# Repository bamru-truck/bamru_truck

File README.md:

# Bamru Truck Wifi Hotspot and Microserver

This guide assumes you've got an Ubuntu laptop with an SD card reader/writer,
and a RPi2 with a USB-WIFI device that runs in master mode.

Github Repo: `https://github.com/cinchcircuits/bamru_truck.git`

The key tools we use to build and maintain the Hotspot:
```
+-------------------+-------------------------------+
| Function          | Tool                          |
+-------------------+-------------------------------+
| RPi configuration | Ansible                       |
| Scripting         | Bash                          |
| Web-Admin UI      | Ruby / Sinatra                |
| Remote pairing    | Tmux / Vim / Wemux            |
+-------------------+-------------------------------+
```

## New RPi Setup

1) load Raspian onto a SD card

https://www.raspberrypi.org/documentation/installation/installing-images/README.md

2) boot the new RPi

3) set the passwd of the 'pi' user to 'pi'

4) enable SSH on the RPi

5) choose a unique hostname & setup DNS or /etc/hosts with the RPi name/address

6) plug in the USB-WIFI and an ethernet cable

7) now you should be able to `ssh pi@<hostname>`

ProTip: create a reusable OS image pre-configured with passwords and account
settings.  Ask Andy for more info.

## Ansible Configuration

1) install latest version of Ansible to your Ubuntu laptop

http://docs.ansible.com/intro_installation.html#latest-releases-via-apt-ubuntu

2) clone the repo and CD to the `playbooks` directory

3) edit `inventory/hosts-<your_username>.ini` - add the RPi hostname and SSID

4) run `./config` to load a bunch of software and configure the hotspot

Notes:
- user-account passwords will be set to 'BamruTruck'

## Using the RPi hotspot

1) You should see the RPi SSID on your laptop network chooser

2) RPi Wifi Passwd is `werescue`

3) You should connect and get a IP address (view with `ifconfig`)

4) Your wifi connection speed should be as good as a commercial hotspot

## Adding a GPS to your hotspot

1) https://github.com/cinchcircuits/bamru_truck/blob/master/playbooks/roles/gpsd

## Adding and using a 2g/3g/4g cell modem to your device

1) https://github.com/cinchcircuits/bamru_truck/tree/master/playbooks/roles/cell_modem_support

## How to Contribute

You'll need a GitHub account, Ubuntu, Command Line savvy, networking skills,
Raspberry Pi know-how, and basic coding skills (HTML, CSS, JS, Ruby).

[Contributing](./docs/Contributing.md)

[Development Notes](./docs/Notes.md)

[Pair Programming](./docs/PairProgramming.md)

[Jenkins](./docs/Jenkins.md)

[Configuring Hostapd and DnsMasq](./docs/HostapdDnsmasq.md)

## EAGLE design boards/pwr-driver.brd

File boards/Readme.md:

-- Rpi Power board

Version 0.1 features:

 - onboard battery support for remote operation
 - ADC (voltage monitor) for incoming voltage and onboard battery. 
 - Ignition detection support
 - Mosfet cutoffs for disconnecting battery and power when battery voltages get low
 - onboard temp monitor
 - onboard RTC support
 - pass through usb connector for powering off cell router
 - Onboard rgb led for use as status indicator. 
 - Unfortunate high current draw at power off (~10 ma). Not green at all, and a concern if the truck is going to go unpowered for many weeks or months. Can run a full car battery dead in 9 months, or make for a slower start after 2 months. 

Possible version 1.0 features:
 - Onboard moisture/humidity sensor
 - onboard gps sensor (not USB)
 - Lower current draw at power off. Shooting for no more than 1 ma.

-- Version 0.1 produced board details
The board has the following features
 - 12v to 4.2 volt step down to charge battery (MPM80)
 - li+ to 5 volt dc to dc (ebay special)
 - can power RPi off of LI+ cell
 - onboard temp monitor LM75b
 - onboard RTC DS1340(DS1370 compatable)
 - onboard adc ads1013

Parts list:
| Part | MPN | link
R3 | 2.2k 0603 | none
R4 | 2.2k 0603 | none
R5 | 20k 0603 | none
R6 | 10k 0603 | none
R7 | 4125 ohm 0603 | http://www.digikey.com/product-detail/en/RR0816P-4121-D-60H/RR08P4.12KDCT-ND/1288210
R8 | 1k 0603 | none
R9 | 5.5k 0603 | none
R10 | 10k 0603 | none
R11 | 30K 0603 | none
R12 | 20k 0603 | none
R13 | 5.5k 0604 | none
RTC | DS1340 | http://www.digikey.com/product-detail/en/DS1340Z-33%2BT%26R/DS1340Z-33%2BT%26RCT-ND/3647911
TEMP | LM75b | http://www.digikey.com/product-detail/en/LM75BD,118/568-4688-1-ND/1993025
ADC | 12-bit ADC | https://www.digikey.com/product-detail/en/ADS1015IDGST/296-25227-1-ND/2174997
PTC | Input protection PTC | http://www.digikey.com/scripts/DkSearch/dksus.dll?Detail&itemSeq=181553660
step-down | 5-15 to 4.2 V | http://www.digikey.com/scripts/DkSearch/dksus.dll?Detail&itemSeq=181553821
Diode | Input diode | http://www.digikey.com/scripts/DkSearch/dksus.dll?Detail&itemSeq=181553817
crystal | RTC crystal | http://www.digikey.com/product-detail/en/AB38T-32.768KHZ/535-9034-ND/675229
RTC cap | supercap for RTC | http://www.digikey.com/product-detail/en/DCK-3R3E224U-E/604-1007-ND/970168

-- I needed to build new modules for this board. 

To do this I did the following steps:
 - upgrade gcc https://somewideopenspace.wordpress.com/2014/02/28/gcc-4-8-on-raspberry-pi-wheezy/
 - did a yum update
 - yum upgrade
 - reboot
 - rpi-update
 - reboot
 - Pulled current kernel source with https://github.com/notro/rpi-source/wiki
 - Specifically: sudo wget https://raw.githubusercontent.com/notro/rpi-source/master/rpi-source -O /usr/bin/rpi-source && sudo chmod +x /usr/bin/rpi-source && /usr/bin/rpi-source -q --tag-update
 - sudo modprobe configs
 - cd to downloaded source folder
 - cp /proc/config.gz .
 - gzip -d config.gz 
 - cat ./config.gz > ./.config
 - make menuconfig
 - enable modules
 - build.. blah blah blah

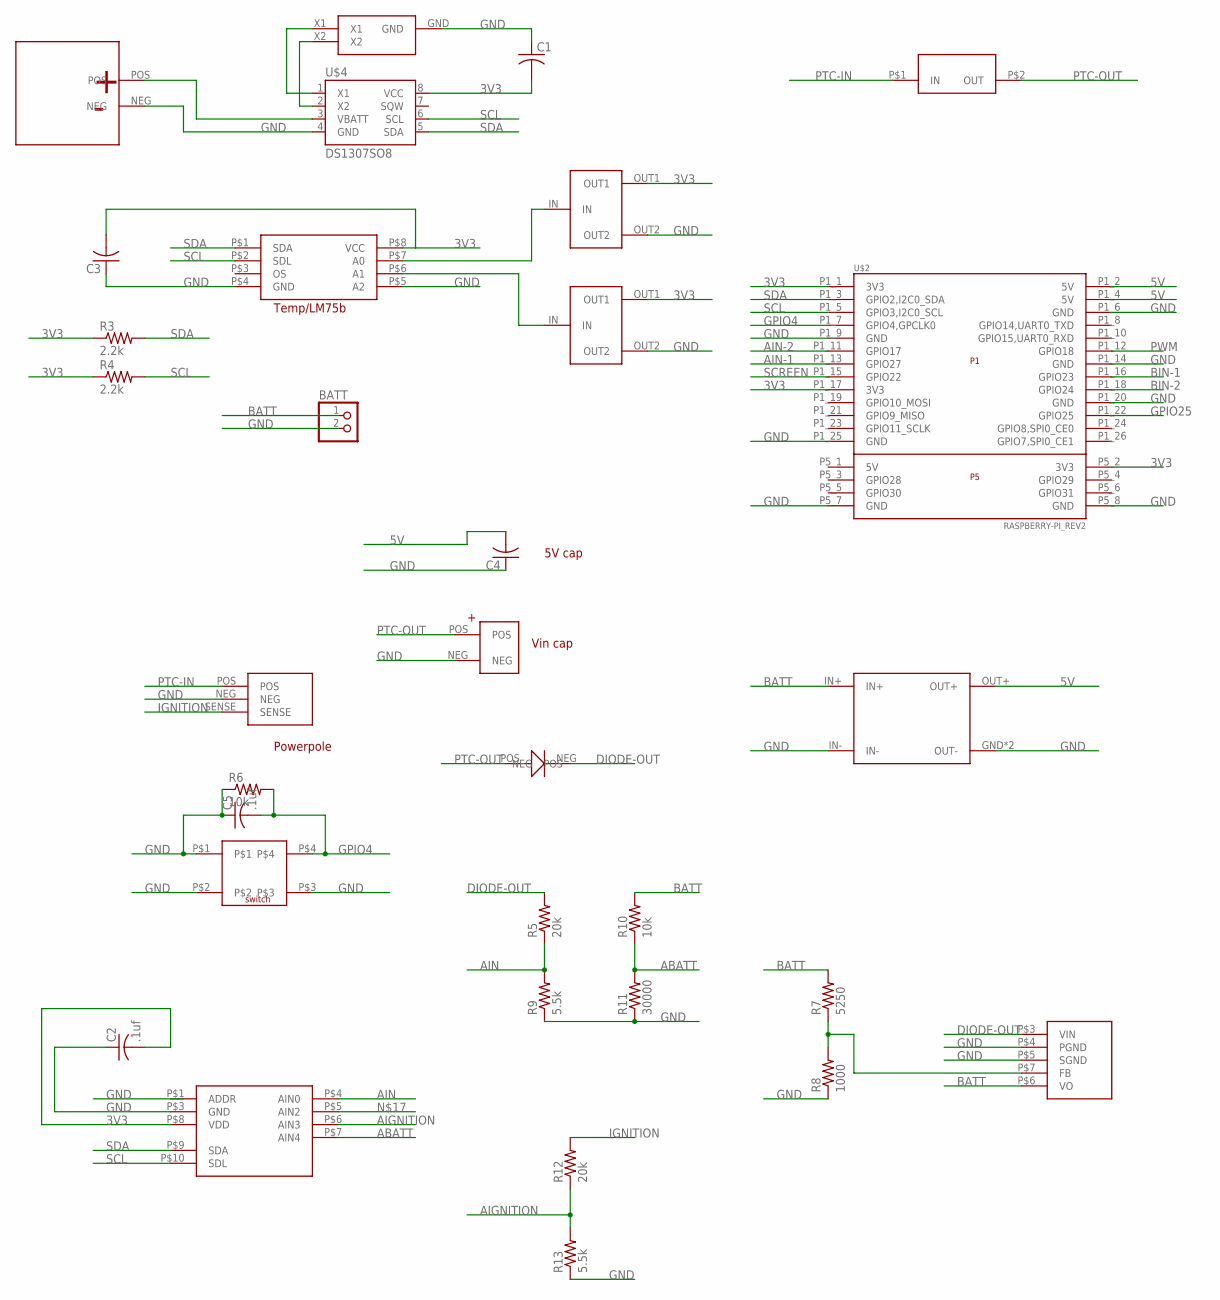
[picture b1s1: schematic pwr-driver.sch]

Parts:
BATT: PINHD-1X2; 1X02
C1: C-USC0805K; C0805K
C2, C5: .1uf; C0603
C3: C-USC0805; C0805
C4: C-USC3216; C3216
R3, R4: 2.2k; R0603
R5, R12: 20k; R0603
R6, R10: 10k; R0603
R7: 5250; R0603
R8: 1000; R0603
R9, R13: 5.5k; R0603
R11: 30000; R0603
U$1: MPM80; TO-220-8L
U$2: RASPBERRY-PI_REV2
U$3: STEP-UP-FROM-AMAZON
U$4: DS1307SO8; SO08
U$5: BATTERY-MS518SE; BATTERY-MS518SE-FL35E
U$6: AB26T-CRYSTAL
U$7: POWERPOLE-WITH-SENSE; POWERPOLE-3
U$8: PTC; PTC-0ZRM0100FF1E
U$9: LM75-BDP-TEMP; TSSOP8
U$10: ADS1013; MSOP-10
U$11: CAP-SMD-100U; CAP-100UF-SMD
U$12, U$13: 0805-3-WAY
U$14: MICRO-SWITCH; BUTTON-MICRO-SWITCH
U$15: DIODE-403; 403

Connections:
3V3: C1.2, C2.2, C3.2, R3.1, R4.1, U$2.P1_1 (3V3), U$2.P1_17 (3V3), U$2.P5_2 (3V3), U$4.8 (VCC), U$9.P$8 (VCC), U$10.P$8 (VDD), U$12.OUT1, U$13.OUT1
5V: C4.2, U$2.P1_2 (5V), U$2.P1_4 (5V), U$3.OUT+
ABATT: R10.1, R11.2, U$10.P$7 (AIN4)
AIGNITION: R12.1, R13.2, U$10.P$6 (AIN3)
AIN: R5.1, R9.2, U$10.P$4 (AIN0)
AIN-1: U$2.P1_13 (GPIO27)
AIN-2: U$2.P1_11 (GPIO17)
BATT: BATT.1, R7.2, R10.2, U$1.P$6 (VO), U$3.IN+
BIN-1: U$2.P1_16 (GPIO23)
BIN-2: U$2.P1_18 (GPIO24)
DIODE-OUT: R5.2, U$1.P$3 (VIN), U$15.NEG
GND: BATT.2, C1.1, C2.1, C3.1, C4.1, C5.1, R6.1, R8.1, R9.1, R11.1, R13.1, U$1.P$4 (PGND), U$1.P$5 (SGND), U$2.P1_6 (GND), U$2.P1_9 (GND), U$2.P1_14 (GND), U$2.P1_20 (GND), U$2.P1_25 (GND), U$2.P5_7 (GND), U$2.P5_8 (GND), U$3.GND (OUT-), U$3.IN-, U$3.OUT-, U$4.4 (GND), U$5.NEG, U$6.GND, U$7.NEG, U$9.P$4 (GND), U$9.P$5 (A2), U$10.P$3 (GND), U$11.NEG, U$12.OUT2, U$13.OUT2, U$14.P$1, U$14.P$2, U$14.P$3
GPIO4: C5.2, R6.2, U$2.P1_7 (GPIO4,GPCLK0), U$14.P$4
GPIO25: U$2.P1_22 (GPIO25)
IGNITION: R12.2, U$7.SENSE
unnamed: U$4.3 (VBATT), U$5.POS
unnamed: U$4.2 (X2), U$6.X2
unnamed: U$4.1 (X1), U$6.X1
unnamed: R7.1, R8.2, U$1.P$7 (FB)
unnamed: U$9.P$7 (A0), U$12.IN
unnamed: U$9.P$6 (A1), U$13.IN
PTC-IN: U$7.POS, U$8.P$1 (IN)
PTC-OUT: U$8.P$2 (OUT), U$11.POS, U$15.POS
PWM: U$2.P1_12 (GPIO18)
SCL: R4.2, U$2.P1_5 (GPIO3,I2C0_SCL), U$4.6 (SCL), U$9.P$2 (SDL), U$10.P$10 (SDL)
SCREEN: U$2.P1_15 (GPIO22)
SDA: R3.2, U$2.P1_3 (GPIO2,I2C0_SDA), U$4.5 (SDA), U$9.P$1 (SDA), U$10.P$9 (SDA)

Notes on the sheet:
5V cap
Vin cap
Powerpole

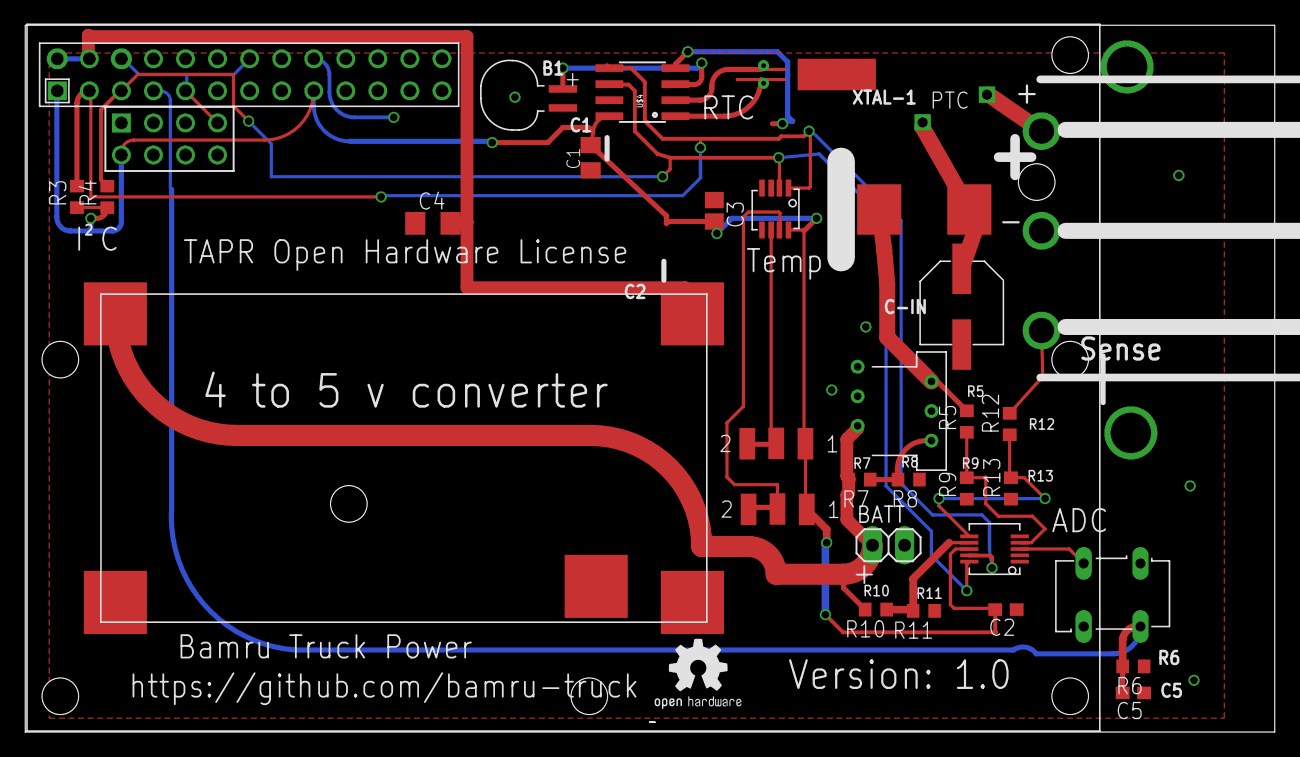
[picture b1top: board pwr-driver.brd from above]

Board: 2 copper layers, 99.0 x 56.0 mm, 33 parts (0 on the bottom side), 20 nets.

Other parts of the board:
U$16: OSHW2

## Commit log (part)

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2015-04-18 first test file
2015-05-03 initial checkin
    Added three new directories:
    1) playbooks - for ansible config stuff
    2) bin - for config scripts TBD
    3) app - for a web app TBD
2015-05-03 updated README instructions
2015-05-03 changed hostnames from rpi to bam
2015-05-03 added apt_update
2015-05-03 add a patch for the broken init.d/hostapd config
2015-05-03 tweak hotspot config
2015-05-04 fix typo
2015-05-04 added ansible_ssh_user
    This eliminates the need to edit the username in the playbook file.
2015-05-04 updated README and config script
2015-05-04 added Hacker Notes
2015-05-04 README tweaks
2015-05-04 tweak playbook
2015-05-05 updated rpi setup
2015-05-07 Ading lines to change destination for iptables rules
2015-05-08 added placeholders for diagnostic scripts
2015-05-10 Added back of hostapd to install.
2015-05-12 modprobe ip_tables
    Iptable commands wouldn't run on initial install because ip_tables
    were not loaded in the kernel. Adding two modifications:
    1) sudo modprobe ip_tables
    2) sudo echo "iptables" >> /etc/modules
2015-05-12 update test scripts
2015-05-18 Adding first gps dev setup script.
2015-05-18 Adding more documentation for gpsd.
2015-05-18 More complete task and readme.
2015-05-18 first checkin for webapp
2015-05-30 iAdding lines to make atheros cards work.
2015-05-30 Adding a few more packages for supporting the end user.
2015-05-31 Moving the hostapd binary selection to the init file for hostapd.
2015-06-09 moved "app" to "web_admin"
2015-06-09 refactored app
2015-06-09 created diretory for web_chat
2015-06-10 updated the process name
2015-06-10 Updating dev env instructions to be more ubuntu/debian consistant.
2015-06-11 added gemrc
2015-06-11 force port 4567
2015-06-11 tweak start/stop
2015-06-11 start/stop tweaks
2015-06-11 tweak config
2015-06-11 flush STDOUT on startup
2015-06-11 tweaks
2015-06-11 deploy script is working
2015-06-17 Added a test to the web admin.
2015-06-17 setup logrotate for web_admin
2015-06-17 Adding cell modem main.yml
2015-06-17 Adding start of modem status python file.
2015-06-17 Adding start of readme for cell modems.
2015-06-18 notes tweak
2015-06-18 Making cell modem file run as a sudo command.
2015-06-19 updated Ansible roles
2015-06-20 Altering hello world as a test
2015-06-20 Adding different erb test with input field.
2015-06-21 Adding reset usb support file to cell modem support.
2015-06-21 fixed README formatting
2015-06-22 added wemux to tmux
2015-06-22 Adding come additional packages to make the admin server run on a virgin rpi.
2015-06-23 can install web_admin from branch
2015-06-23 added tmux sessions
2015-06-26 updated web_admin gem install task
2015-06-26 updated portfwd script
2015-06-26 updated web_admin start-stop scripts
2015-06-26 tweak start/stop script
2015-06-26 proper restart of web_admin_d on redeploy
2015-06-27 tweaked deploy/restart task
2015-06-27 fixed typo
2015-06-27 refactored web_admin views
2015-06-27 added menu option for /token
2015-06-27 extracted ops data
    Ops data (log and pid files) was stored in the app directory,
    which is compleetely destroyed and rebuilt during every deploy.
    In order to get the ops data to be persistent, it has been moved.
    Previous layout:
    /home/deploy/apps/web_admin -> application
    /home/deploy/apps/web_admin/logs -> log files
2015-06-27 updated README files
2015-06-27 fixed option-parsing bug
2015-07-07 commented cell-modem coverage
2015-07-07 commented failing hotspot_rpi role
2015-08-03 Adding ino file for first arduino test board.
2015-08-03 Adding first seemingly working code for a rebooter.
2015-08-03 Altering usage on the way the relay is handled.
2015-08-03 Adding base files for use with automated executions.
2015-08-07 Reorganize documentation
2015-08-10 Add 'playbook' option
    With our multi-phase plan, we need to handle multiple playbooks, one for
    each phase.
    The `config` script was written to run with a single, hardedcoded
    playbook name: `rpi.yml`.
    This change allows for multiple playbook files, with the file naming
    convention like `rpi-<name>.yml`.
2015-08-10 Update tasks in default playbook
2015-08-10 Add serverspec
2015-08-11 Updating automation yml file.
2015-08-11 this is a nice change, you should totally merge it
2015-08-14 Adding text to case, and adding filets
2015-08-14 Enlarged text on top of box.
2015-08-17 Add `colored` gem for terminal output
2015-08-17 Remove verbose settings from rake tasks
2015-08-17 Configure roles and playbook for phase1
2015-08-18 Update phase1 spec
2015-08-18 Update phase1 config
2015-08-29 Update roles
2015-08-30 Add vars_dump role
2015-08-30 Update playbook
2015-08-30 Add git role
2015-08-30 Fix ansible issue
2015-08-30 Update NetBoot
2015-08-30 Change "automation_hardware" to "powercycle"
2015-08-31 Add ci_util
2015-08-31 Update reset script
2015-08-31 Update scripts
2015-08-31 Add gen_env
2015-08-31 Update CI scripts
2015-08-31 Add util script
2015-09-02 Add wemo scripts to powercycle
2015-09-02 Add ouimeaux
2015-09-02 Update doc
2015-09-03 Add file backup
2015-09-04 Update NetBoot docco
2015-09-04 Altering what hostapd binary is used for atheros cards.
2015-09-05 Update serverspec/Rakefile
2015-09-05 Update serverspec
2015-09-05 Add PairProgramming docco
2015-09-05 Tweak docco
2015-09-05 Add ci/env.yml
2015-09-06 Modify powercycle
2015-09-06 Update ci
2015-09-06 Removing broken gobi loader from cell modem support.
2015-09-06 removing debug messages from prep_cmdline
2015-09-06 Update env
2015-09-07 WIP Update
2015-09-07 Show CI user
2015-09-07 Test gen_env
2015-09-07 Show hostname
2015-09-07 Add host setup script
2015-09-07 Tweak powercycle
2015-09-09 Removing aprs-post dir
2015-09-09 Adding example python files instead of submodules config.
2015-09-09 Adding working single report python script pulling from gpsd
2015-09-10 Prep for sdconfig refactoring
    The next series of commits will eliminate the need to perform any
    configuration steps on the RPi itself. The new process will be:
    1. install the base OS onto the SD card
    2. run a config script that configures the SD card
    3. install the SD card into the RPi, and boot
2015-09-11 Adding more servers to single report
2015-09-11 Adding partially correct email sender script.
2015-09-11 Add slightly better formatting of sending email in test send.
2015-09-12 Convert Ruby to Bash
2015-09-12 Update sdconfig scripts
2015-09-12 Adding untested code to exercise direwolf gpsd and call home scripts.
2015-09-14 Turn on ansible debugging
2015-09-15 Update CI docco
2015-09-15 Remove wlan0 from serverspec
2015-09-15 Add first draft of homegrown CI server
    Keep the home-grown server code around, for possible use in the future.
2015-09-15 Add hostname existance test
2015-09-15 Cleanup env.yml
2015-09-15 Add error/guard to check for LOCAL_IP address
2015-09-15 Extend timeout from 5 cycles to 9
2015-09-15 Add relative execution
    Previously, all scripts had to be run from the 'base' path
    (<whatever>/bamru_truck). This was inconvenient for development and
    testing.
    This change allows more flexibility, so that scripts can be run from any
    direcory. All of these examples work:
    - from 'bamru_truck' => ci/powercycle
2015-09-15 Add password update
2015-09-15 Fix msg bug in run_ansible
2015-09-15 Clean know_hosts
2015-09-16 First working version of HomeGrown CI
    See the README.md file for more info.
2015-09-16 Add HGCI dashboard
2015-09-16 Workaround to a strange bug
    During ci/all, the ansible run fails, unexplicably, when trying to run
    the kernel/iptables update commands.
    The failure pattern is:
    - it fails the first time
    - when you run the failed command immediately the second time, it works
    - the command never fails when run from the command line instead of from
2015-09-16 Fix sd_root bug
    Fix so that the sd_* environment variables (sd_root, sd_boot, sd_base)
    are only generated if the SD card is present in the machine.
2015-09-16 Restart running HGCI server processes
2015-09-16 Add tmux to the dev-server setup
2015-09-16 Add exit message for long-running scripts
2015-09-16 Rename doc file for easier understanding
2015-09-16 Add elapsed time to wrap-up function
2015-09-16 Adding dummy line for test
2015-09-17 Adding first, rough turn of gpsd support
2015-09-17 Add time display to HTML pages
2015-09-17 Remove outdated functions
2015-09-17 Add apt-cacher-ng support
2015-09-17 Update SSH config docco
2015-09-17 Fix aptcacher bug
2015-09-17 Removing call home from phase 1
2015-09-17 Fix bad aptcacher bug
2015-09-17 Add curl to package list
2015-09-17 Enhance SSH support
    - add additional SSH functions
    1) scrub_ssh_known_hosts
    2) display_ssh_config_tip
    - use the SSH functions in ci and sdconfig scripts...
2015-09-18 Add directory size check
2015-09-18 Fix bug with export_dir_validation
2015-09-18 Refactor serverspecs
2015-09-18 Fix ansible text buffering issue
    When running ANSIBLE in CI (Jenkins or HGCI), stdout is buffered until
    the ansible run finishes. This fix causes stdout to dump intermediate
    results, making it possible to watch live ansible runs.
2015-09-18 Add URL with problem description
2015-09-18 Add rpi-phase2.yml
2015-09-19 Add JQ text processing utility
    JQ is a text-processing utility, like sed, awk or tr. JQ specializes in
    procesing JSON text.
    This commit adds a JQ role. On Ubuntu, it installs jq from apt-get. On
    RPi, it installs a pre-compiled version of jq.
2015-09-21 Change log file location
    Log file name now associated with remote port, to handle multiple
    portfwd scripts running concurrently.
2015-09-21 Refactor hgci
    - dashboard now handles attachment/reattachment
    - server and workers now kill prior instances (if they exist) and
    restart
2015-09-21 Add tracker app
2015-09-22 Refactor for readability
2015-09-22 Add client scripts for tracker
2015-09-22 Add ansible roles for tracker
2015-09-22 Remove thin web server
2015-09-22 Add BATS testing framework
    BATS is a testing framework for BASH scripts. Learn more about BATS at
    https://github.com/sstephenson/bats.
    This commit has two elements:
    - BATS installation - in bin/setup_dev_server
    - example test - in bin/tests
    BATS tests can be built for any BASH function or command-line program.
2015-09-22 Update shebangs
    Change #!/bin/bash to #!/usr/bin/env bash
2015-09-22 Remove outdated code
2015-09-22 Add BATS tests to ci/all
2015-09-22 Fix tracker client bugs
2015-09-22 Add hasGPS column
2015-09-22 Add color codes to tracker webapp
2015-09-23 Change setblock to textblock for readability
2015-09-24 Update exit message
2015-09-25 Fix time-bugs in server
2015-09-28 gpsd playbok now adds critical udev rule, and no longer requires a reboot to function.
2015-09-28 Enabling syntax highlighting on vim by default.
2015-09-28 Log no-data errors to console
2015-09-28 Rewrite port_forward script from ruby to bash
2015-09-28 Add port_forward to ansible
    This commit adds an ansible playbook to auto-install the port_forward
    script onto the RPi.
    The install location is /usr/local/bin/port_forward
    ALSO: now there is a 'pi' user on the proxy server. (with the normal pi
    password...)
2015-09-28 Fix reporter bugs
    - hostname: extract TLD from FQDN
    - default lon: fix bug in default lon generation
2015-09-29 dding start of parts lib for breakout board.
2015-10-02 Converted to three pin powerpole.
2015-10-03 Adding support for AR9271 stick for hostapd.
2015-10-04 Add process monitoring for TRACKER app
    The tracker app relies on three processes:
    1) the server (web application)
    2) the worker (sends email alerts)
    3) the tunnel (setup port forwarding)
    This commit adds scripts that monitor and restart TRACKER processes in
    case of failure.
2015-10-04 Fix tracker script bugs
2015-10-05 Fix bats bugs
2015-10-06 Add logrotate to cron
2015-10-07 Update sdconfig
2015-10-07 Fix usage message
2015-10-11 Adding Version 1.0 boards with the submitted gerbers.
2015-10-11 Fix HGCI bugs
2015-10-12 dding description of Resistor dividors to schematic.
2015-10-12 Started adding notes about the parts list of the first board.
2015-10-22 Add mobile tracks
2015-10-22 Update tracker app
2015-11-13 Adding start of power board support files.
2015-11-21 updating adc link on boards readme
2015-11-22 Adding install for lm sensors.
2015-11-29 Adding files for reading ADC

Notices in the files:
boards/pwr-driver.brd:
TAPR Open Hardware License
